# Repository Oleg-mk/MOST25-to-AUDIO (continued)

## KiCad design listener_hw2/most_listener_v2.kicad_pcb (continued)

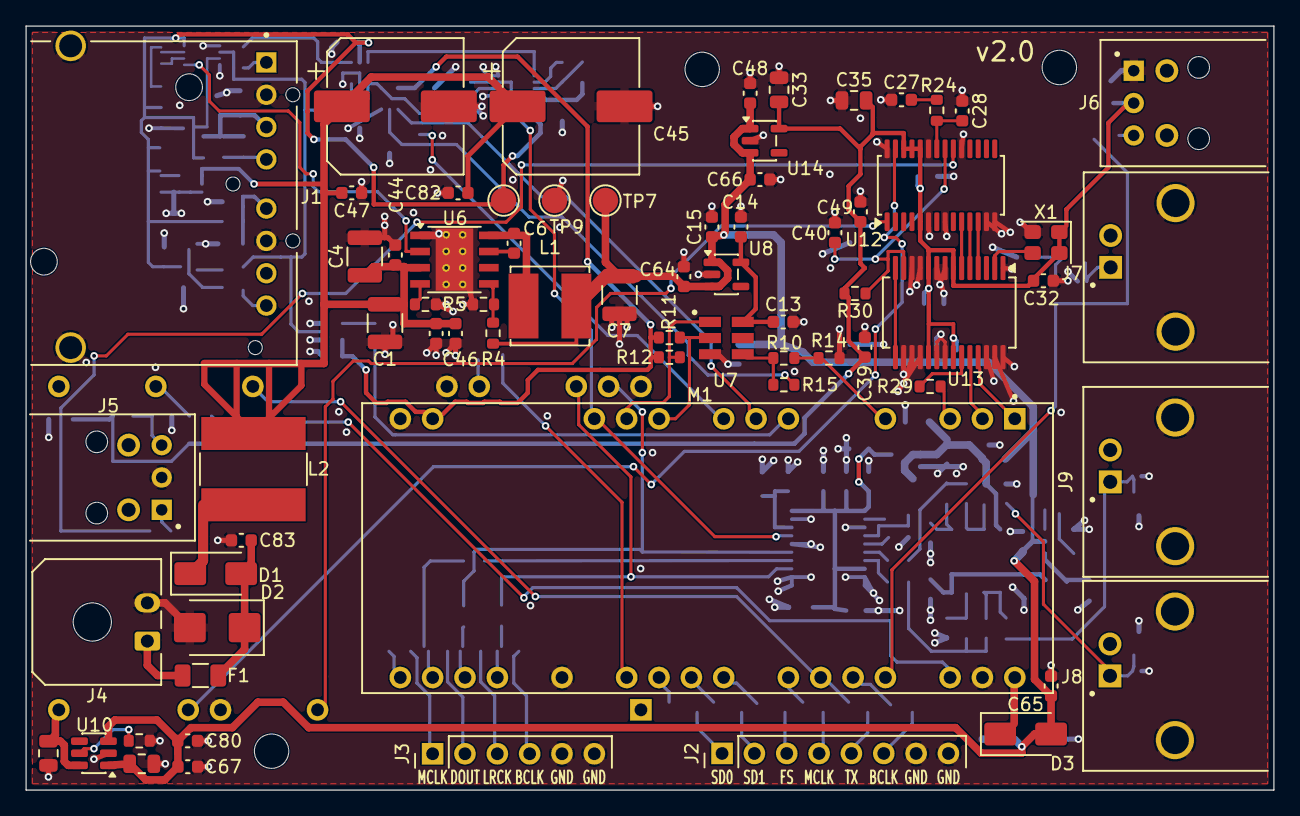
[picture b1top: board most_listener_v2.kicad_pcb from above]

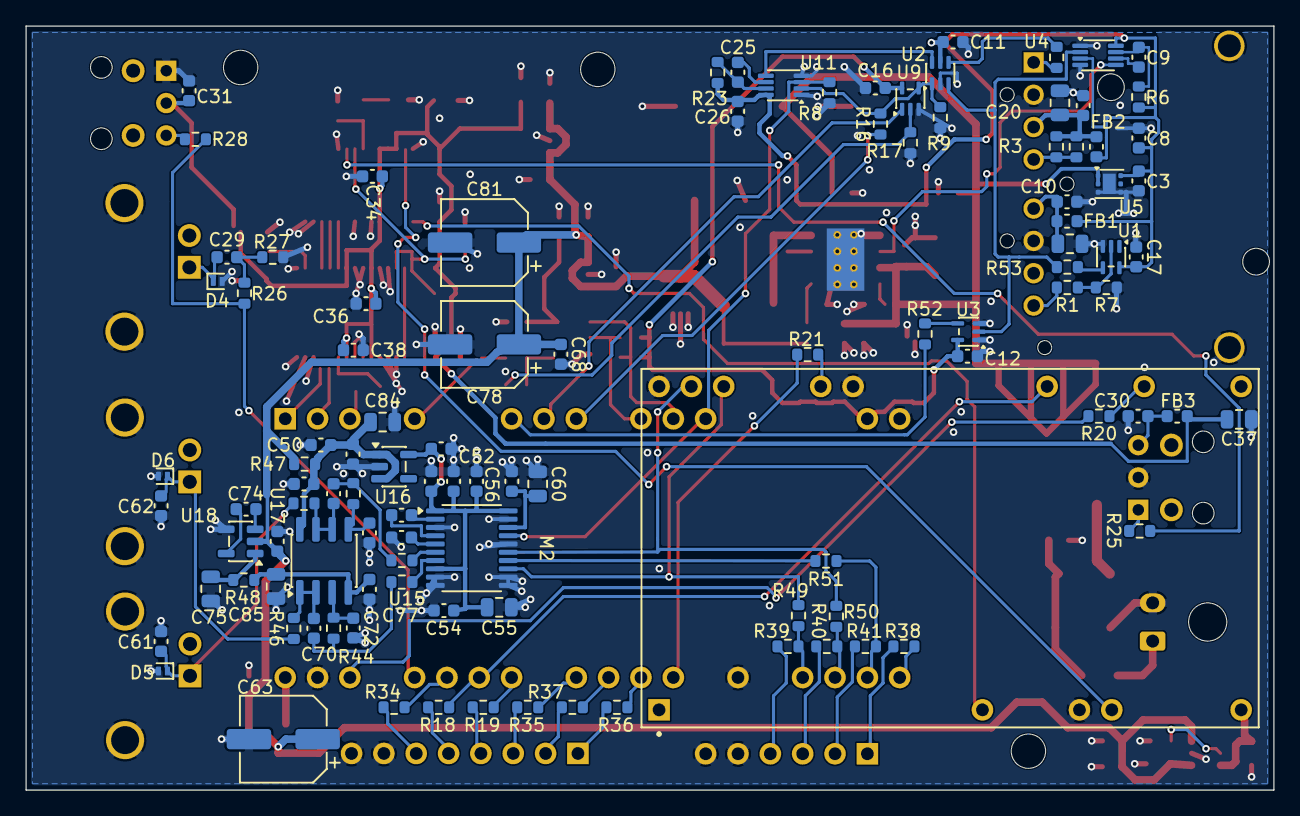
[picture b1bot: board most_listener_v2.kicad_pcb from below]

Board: 4 copper layers, 98.0 x 60.0 mm, 180 parts (107 on the bottom side), 111 nets.

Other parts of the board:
H1, H2, H3: MountingHole_2.7mm_M2.5

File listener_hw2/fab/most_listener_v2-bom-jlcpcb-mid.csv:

Comment,Designator,Footprint,LCSC Part #,Manufacturer Part
10u 100V,C1,C_1210_3225Metric,C576517,"Murata GRM32EC72A106KE05L, X7S"
100n 100V,"C2,C43,C46,C47,C82,C83",C_0603_1608Metric,C15725,"Samsung CL10B104KC8NNNC, X7R"
2u2,"C3,C53,C57,C58",C_0603_1608Metric,C23630,"Samsung CL10A225KO8NNNC, 16 V X5R"
4u7 100V,C4,C_1210_3225Metric,C385986,"Taiyo Yuden HMK325C7475KMHPE, X7S"
100n,"C6,C8,C10,C11,C12,C13,C16,C17,C19,C26,C29,C31,C52,C54,C56,C59,C64,C65,C66,C67,C68,C76,C77,C79,C80",C_0603_1608Metric,C14663,"Yageo CC0603KRX7R9BB104, 50 V X7R"
47u 10V,C7,C_1210_3225Metric,C77101,"Murata GRM32ER61C476KE15L, 16 V X5R"
1u,"C9,C14,C15,C48,C49,C50,C51,C73,C74",C_0603_1608Metric,C15849,"Samsung CL10A105KB8NNNC, 50 V X5R"
10u,"C18,C20,C60",C_0805_2012Metric,C15850,"Samsung CL21A106KAYNNNE, 25 V X5R"
10u 16V,C23,C_0805_2012Metric,C15850,"Samsung CL21A106KAYNNNE, 25 V X5R"
10u 6V3,C24,C_0805_2012Metric,C15850,"Samsung CL21A106KAYNNNE, 25 V X5R"
1n,C25,C_0603_1608Metric,C1588,"Samsung CL10B102KB8NNNC, 50 V X7R"
100u 63V,"C44,C45",CP_Elec_10x10.5,C53330124,"SamYoung CLZ 63V 100uF 10x10, 125 C"
4u7,"C55,C75",C_0805_2012Metric,C1779,"Samsung CL21A475KAQNNNE, 25 V X5R"
2n2,"C61,C62",C_0603_1608Metric,C2991172,"FH 0603CG222J500NT, C0G"
100u 16V,"C63,C78,C81",CP_Elec_6.3x7.7,C359220,SamYoung BLA 16V 100uF 6.3x6
820p,"C69,C70",C_0603_1608Metric,C99081,"FH 0603CG821J500NT, C0G"
390p,"C71,C72",C_0603_1608Metric,C1667,"FH 0603CG391J500NT, C0G"
SS34,"D1,D3",D_SMA,C8678,MDD SS34
SMBJ36A,D2,D_SMB,C135070,Diodes SMBJ36A-13-F
PESD5V0S1BL,"D4,D5,D6",D_SOD-882,C84374,"Nexperia PESD5V0S1BL,315"
2A T,F1,Fuse_1206_3216Metric,C2925010,"TLC F12T2, slow blow, 72 V"
600R,"FB1,FB2",L_0603_1608Metric,C1002,Sunlord GZ1608D601TF
15u,L1,L_Bourns_SRN6045TA,C1330797,Bourns SRN6045TA-150M
22u,L2,L_Bourns-SRN8040_8x8.15mm,C2041547,Bourns SRN8040-220M
150,"R1,R2",R_0603_1608Metric,C22808,UNI-ROYAL 0603WAF1500T5E
27k,"R3,R42",R_0603_1608Metric,C22967,UNI-ROYAL 0603WAF2702T5E
100k,"R4,R6,R7",R_0603_1608Metric,C25803,UNI-ROYAL 0603WAF1003T5E
23k2,R5,R_0603_1608Metric,C23346,UNI-ROYAL 0603WAF2322T5E
10k,"R8,R9,R14,R17,R23",R_0603_1608Metric,C25804,UNI-ROYAL 0603WAF1002T5E
22,"R10,R15",R_0603_1608Metric,C23345,UNI-ROYAL 0603WAF220JT5E
2k,"R11,R12",R_0603_1608Metric,C22975,UNI-ROYAL 0603WAF2001T5E
33,"R16,R18,R19,R20,R21,R28,R34,R35,R36,R37,R38,R39,R40,R41",R_0603_1608Metric,C23140,UNI-ROYAL 0603WAF330JT5E
24k9 1%,R22,R_0603_1608Metric,C25962,UNI-ROYAL 0603WAF2492T5E
100,"R45,R46",R_0603_1608Metric,C22775,UNI-ROYAL 0603WAF1000T5E
240,R26,R_0603_1608Metric,C23350,UNI-ROYAL 0603WAF2400T5E
110,R27,R_0603_1608Metric,C22781,UNI-ROYAL 0603WAF1100T5E
64k9 1%,R31,R_0603_1608Metric,C14891,UNI-ROYAL 0603WAF6492T5E
4k7,"R32,R33,R43,R44",R_0603_1608Metric,C23162,UNI-ROYAL 0603WAF4701T5E
74LVC1G34,U1,SOT-353_SC-70-5,C353880,TI SN74LVC1G34DCKR
74LVC1G157,U2,SOT-363_SC-70-6,C135822,"Nexperia 74LVC1G157GW,125"
74LVC1G125,U3,SOT-353_SC-70-5,C7833,TI SN74LVC1G125DCKR
74LVC1G123,"U4,U11",VSSOP-8_2.3x2mm_P0.5mm,C352969,TI SN74LVC1G123DCUR
TPS7B8133DRV,U5,WSON-6-1EP_2x2mm_P0.65mm_EP1x1.6mm,C2876250,TI TPS7B8133DRVR
LMR38020F,U6,Texas_HSOP-8-1EP_3.9x4.9mm_P1.27mm_ThermalVias,C5149193,TI LMR38020FDDAR
Si514,U7,Si514_3.2x5_2.5x3.2,,"Skyworks Si514, consigned (see the README)"
LP5907MFX-3.3,"U8,U14,U16",SOT-23-5,C130005,TI LP5907QMFX-3.3Q1
74LVC1G79,U9,SOT-353_SC-70-5,C2677837,TI SN74LVC1G79DCKR
TPS2553DBVR,U10,SOT-23-6,C55266,TI TPS2553DBVR
PCM5102A,U15,TSSOP-20_4.4x6.5mm_P0.65mm,C107671,TI PCM5102APWR
OPA1678,U17,SOIC-8_3.9x4.9mm_P1.27mm,C192421,TI OPA1678IDR
TPS60403,U18,SOT-23-5,C11338,TI TPS60403DBVR

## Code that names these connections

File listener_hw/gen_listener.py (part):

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    # unconfigured (its pins float or pull up).
    u11 = one_shot(sh, "U11", 85.09, "R23", "10k", "C25", "1n", "C26", "TX_SEL")
    clr, bb, aa = u11.p("3"), u11.p("2"), u11.p("1")
    sh.wire(clr, (218.44, clr[1])); sh.label("LOCK", (218.44, clr[1]), "L")
    r8 = sh.at_pin("R", "R8", "10k", "1", (223.52, clr[1]), fp=SMD["R"],
                   ref_at=(222.25, clr[1] + 2.54), val_at=(222.25, clr[1] + 5.08),
                   fjust=("right", "right"))
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    y = u1.p("4")
    node = (y[0] + 12.7, y[1])
    sh.wire(y, node)
    sh.wire(node, (node[0], y[1] - 12.7)); sh.label("RX_BUF", (node[0], y[1] - 12.7), "R")
    # MUX: I0 = RX_BUF (bypass), I1 = TX_REGEN, S = TX_SEL (U11: LOCK and TX toggling)
    u2 = sh.at_pin("MUX157", "U2", "74LVC1G157", "3", (node[0] + 22.86, y[1]),
                   fp="Package_TO_SOT_SMD:SOT-363_SC-70-6")
    sh.wire(node, u2.p("3"))
    i1, s_ = u2.p("1"), u2.p("6")
    xa, xl = i1[0] - 5.08, i1[0] - 17.78
    sh.wire(i1, (xa, i1[1]), (xl, i1[1])); sh.label("TX_REGEN", (xl, i1[1]), "L")
    sh.wire(s_, (xl, s_[1])); sh.label("TX_SEL", (xl, s_[1]), "L")
    # R9: TX_REGEN low while U9 is unpowered (Ioff: its output floats), for
    # U2's I1 and U11's B alike
    r9 = sh.at_pin("R", "R9", "10k", "1", (xa, s_[1] + 5.08), fp=SMD["R"])
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        else:
            sh.nc(p)
    sh.text("Pins 1..20 / 21..40 top to bottom, from the USB-C; name = the GW2AR pin + what the module has on it (data sheet v1.3).", 279.4, 184.15, 1.27)
    sh.text("The ring and the Si514 on the LCD pins only (an empty connector): LOCK on 31, S/PDIF on 42. HSPI, 54..56 (the module amplifier's inputs; PA_EN = 51 keeps it off), EDID 52/53: UART, MCLK, I2S, SD1, DIN2.", 279.4, 187.96, 1.27)
    sh.text("CLK_1024 (Si514) -> 77 (GCLKT_1). TX_FB -> 25 through IDES8 (1.26 ns); it takes the pair, so 26 is not connected.", 279.4, 191.77, 1.27)
    sh.text("D3: the USB and 5V_SW are never joined; U6 gives 5.3 V, the module gets ~5.0 V.", 279.4, 195.58, 1.27)
    sh.text("v1.2: lines to the right leave the right row as J2, J3, DAC, host; U13's (SRC_BCLK, SRC_LRCK, DIN2) the left row, over M1.", 279.4, 110.49, 1.27)
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    # v1.2: everything the FPGA meets on the header row that faces M1 (pads
    # 20..38), each opposite its FPGA pin: the ring-locked I2S clocks and the raw
    # control blocks in; the commands and our audio out, each through 33R at the
    # FPGA pin (R20, R21 sit under M1); OPT_ERR and (v1.3) OPT_NPCM from U12 on the far row
    for pad, name in (("21", "I2S_LRCK_F"), ("22", "I2S_BCLK_F"), ("32", "UART_TX_F")):
        sh.lbl(name, m2.p(pad), 7.62, "R")
    for pad, ref, name in (("35", "R20", "UART_RX_F"), ("25", "R21", "I2S_DIN_F")):
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
    # ---- S/PDIF out: one FPGA pin (DRIVE 16) into the TOSLINK transmitter and the coax divider
    n1 = (271.78, 323.85)
    sh.label("SPDIF_F", (264.16, n1[1]), "L"); sh.wire((264.16, n1[1]), n1)
    r28 = sh.at_pin("R", "R28", "33", "1", (n1[0] + 2.54, n1[1]), r=90, fp=SMD["R"])
    sh.wire(n1, r28.p("1"))
    j6 = sh.at_pin("TOSLINK_TX", "J6", "FCR684205T", "3", (r28.p("2")[0] + 7.62, n1[1]), fp=f"{LIB}:{FP_CLIFF}",
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                    ref_at=(314.96, 360.68), val_at=(314.96, 363.22), fjust=("right", "right"))
    sh.up("3V3_DA", r30.p("1"), 2.54)
    c40 = sh.at_pin("C", "C40", "1u", "1", r30.p("2"), fp=SMD["C"]); sh.gnd(c40.p("2"))
    sh.wire(r30.p("2"), (312.42, 365.76)); sh.label("RST_AIN", (312.42, 365.76), "L")
    caps = [("C31", "100n", SMD["C"]), ("C32", "100n", SMD["C"]), ("C33", "10u", "Capacitor_SMD:C_0805_2012Metric"),
            ("C34", "100n", SMD["C"]), ("C35", "10u", "Capacitor_SMD:C_0805_2012Metric"),
            ("C36", "100n", SMD["C"]), ("C37", "10u", "Capacitor_SMD:C_0805_2012Metric"),
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        q = (xx - 5.08, y)
        sh.wire(tp.p("1"), q); sh.gnd(q, 2.54)
    sh.text("Bench probe points: the 3V3_AON and 5V_SW rails, ground. None on the ring's lines: a stub on their edges", 414.02, 353.06, 1.27)
    sh.text("would hurt. RX_BUF at U1 pin 4, TX_SEL at U2 pin 6, TX_REGEN and RT_CLK at U9 and at M1 (TX_FB).", 414.02, 356.87, 1.27)


def line_out_block(sh):
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    sh.wire(pin_in, nin); sh.up("5V_SW", nin, 2.54)
    c73 = sh.at_pin("C", "C73", "1u", "1", nin, fp=SMD["C"]); sh.gnd(c73.p("2"))
    nout = (round(pin_out[0] + 5.08, 3), pin_out[1])
    sh.wire(pin_out, nout); sh.up("VNEG_A", nout, 2.54)
    c75 = sh.at_pin("C", "C75", "4u7", "1", nout, fp="Capacitor_SMD:C_0805_2012Metric"); sh.gnd(c75.p("2"))
    cp, cm = u18.p("5"), u18.p("3")
    c74 = sh.at_pin("C", "C74", "1u", "1", (cp[0], round(cp[1] - 2.54, 3)), r=90, fp=SMD["C"])
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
